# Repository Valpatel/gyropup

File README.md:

<div align="center">

<h1 id="gyropup"><picture style="display:block;max-width:640px;margin:0 auto"><source media="(prefers-reduced-motion: reduce)" srcset="docs/img/hero/gyropup-title-still.svg"></picture></h1>

<p>
<picture style="display:block;max-width:640px;margin:0 auto"><source media="(prefers-reduced-motion: reduce)" srcset="docs/img/navigation/project-map-still.svg"></picture>
<a href="https://cad-agent.valpatel.com/"><picture style="display:block;width:142px;max-width:100%;margin:10px auto"><source media="(prefers-reduced-motion: reduce)" srcset="docs/img/hero/made-with-cad-agent-still.svg"></picture></a>
A fictional playground. <a href="docs/program/physical-progress.md">Follow the real build evidence.</a><br>
<a href="https://gyropup.com/designer/sim.html">Play</a> · <a href="https://gyropup.com/designer/build.html">Build</a> · <a href="docs/README.md#design-and-qualification">Understand</a> · <a href=".github/CONTRIBUTING.md">Contribute</a>
</p>

</div>

## What is it?

A research robot designed to balance on two wheel-legs, with a foam-ball turret: CAD and simulation in the open.
Explore the [browser playground](https://gyropup.com/designer/sim.html), the
[design](docs/README.md#design-and-qualification) and [dated physical evidence](docs/program/physical-progress.md).

<p align="center">
<br>
Committed CAD baseline · <a href="docs/guide/project-overview.md#keeping-the-design-illustration-current">Source and context</a> · <a href="https://github.com/Valpatel/gyropup/issues/193">Battery placement work</a>.
</p>

## Why is it cool?

- Wheel-legs bring rolling, stepping and balance into one research problem.
- Open models make the design explorable in your browser.
- Gyropup evolves with cad-agent through good sources, evaluation, independent review and reusable methods.

Follow the [leg, turret and body build paths](docs/guide/project-overview.md#follow-the-build),
or browse the [published progress and reports](https://gyropup.com/designer/progress.html).

## How do I join in?

Start with [Contributing](.github/CONTRIBUTING.md), then choose a scoped issue from
[program #31](https://github.com/Valpatel/gyropup/issues/31). The [project guide](docs/guide/project-overview.md)
and [documentation map](docs/README.md) lead to the hardware, software, tools, tests and local website workflow.

**Unsafe research prototypes; not for sale.** Read the [prototype warning](docs/guide/prototype-safety.md).

[MIT](LICENSE) · [Licensing and vendor boundaries](docs/guide/project-overview.md#licence).

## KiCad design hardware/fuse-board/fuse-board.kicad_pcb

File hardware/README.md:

# Hardware: one folder per component

Physical design, component specifications and generated artifacts live here in separate homes:
[CAD](cad/README.md), [catalog](catalog/SCHEMA.md), [design inputs](designs/),
[generated exports](exports/) and [supplier acquisition records](vendor/).
Supplier payloads retain their original license and exclusion boundaries. Firmware and host control live in [software](../software/README.md).

Everything the repository knows about each bought or owned component, in one place per part: where its manual is,
how it connects, how it is configured, which code drives it, which units are in hand and how to bring it up. The
design itself stays where it is (the catalog, the docs, the CAD); these folders point at it and hold the parts that
belong to one component: its versioned config, its inventory and its bring-up page.

```mermaid
flowchart TB
  HW["hardware/"] --> A["actuators/"] & D["drives/"] & S["sensors/"] & P["power/"] & C["compute/"] & M["comms/"] & T["turret/"]
  A --> A1["rs04"] & A2["wheel-hub-motor"]
  D --> D1["flipsky-75100"]
  S --> S1["vn100-imu"] & S2["vlp16-lidar"] & S3["d435-depth-camera"]
  P --> P1["ina228-monitor"] & P2["dcb609-packs"]
  C --> C1["balance-mcu"] & C2["robot-computer"]
  M --> M1["pcan-usb"]
  T --> T1["turret-controller"]
  HW --> PCB["PCB projects (unchanged):<br/>fuse-board, carrier-packaging, carrier-pan-protection"]
```

## The map

| Folder | Component | In hand | State |
|---|---|---|---|
| [actuators/rs04/](actuators/rs04/README.md) | RobStride RS-04 leg motors | 4 (arrived 2026-11-03) | profiles, inventory, [bring-up](actuators/rs04/bring-up.md), the [motor tool](../docs/software/rs04-motor-tool.md) |
| [actuators/wheel-hub-motor/](actuators/wheel-hub-motor/README.md) | 10 in hoverboard-class hub motors (D69) | none | to buy and measure (W1) |
| [drives/flipsky-75100/](drives/flipsky-75100/README.md) | Flipsky 75100 VESCs for the wheels | none | VESC Tool settings recorded |
| [sensors/vn100-imu/](sensors/vn100-imu/README.md) | VectorNav VN-100 Rugged | 1 (the owner's) | boot registers recorded |
| [sensors/vlp16-lidar/](sensors/vlp16-lidar/README.md) | Velodyne VLP-16 | 1 (the owner's) | interfaces only |
| [sensors/d435-depth-camera/](sensors/d435-depth-camera/README.md) | RealSense D435 x 2 | 2 (the owner's) | interfaces only |
| [power/ina228-monitor/](power/ina228-monitor/README.md) | INA228 bus monitor and its shunt | none | shunt builds recorded |
| [power/dcb609-packs/](power/dcb609-packs/README.md) | DeWalt DCB609 packs and dock adapters | 2 (the owner's) | firmware limits recorded |
| [compute/balance-mcu/](compute/balance-mcu/README.md) | STM32G474 balance MCU board and CAN transceivers | none | pins and buses |
| [compute/robot-computer/](compute/robot-computer/README.md) | the robot's Jetson (J501 + AGX Orin in the design) | 1 (the owner's J501) | [hardware/deploy/jetson](../software/deploy/jetson/README.md); which Jetson is open |
| [comms/pcan-usb/](comms/pcan-usb/README.md) | PEAK PCAN-USB configuration adapter | 1 (the owner's) | used by the motor tool |
| [turret/turret-controller/](turret/turret-controller/README.md) | the turret's Feather M4 CAN electronics | none | a pointer to the turret docs |

**PCB projects** stay where they are, with their own layout: [fuse-board/](fuse-board/) (the generated KiCad fuse and
shunt board, D60; its doc is [docs/body-fuse-board.md](../docs/body/body-fuse-board.md)),
[carrier-packaging/](carrier-packaging/README.md) (issue #96) and
[carrier-pan-protection/](carrier-pan-protection/README.md) (issue #87). They are boards being designed, not components
bought; moving them under a category would break their build scripts' paths and their links for no gain, so they
are listed here and left alone.

## The skeleton every component folder keeps

`tools/check-hardware.py` checks it in CI (workflow `jetson-deploy`): every folder under a category has these, every
JSON file parses and names a `gyropup.*` schema, every relative link resolves, every sourced value in a
`gyropup.config/1` file still matches its source, and this map lists the folder. The RS-04 profiles
(`gyropup.rs04-profile/1`) are checked the same way by `python -m rig.rs04_profiles` and `rig/tests/test_rs04_vectors.py`.

| Part | What goes in it |
|---|---|
| `README.md` | a short intro, a diagram, then these sections in this order: **References**, **Interfaces**, **Config and profiles**, **Driver**, **Inventory**, **Bring-up and tests**, **Open questions** |
| References | where the manual, datasheet and CAD come from, **cited, never redistributed**: vendor files stay local, with a `SOURCE.txt` under `references/vendor/` saying where and when |
| `interfaces.md` | power, connectors, pinouts, buses and mounting, each row with its source |
| `config/` or `profiles/` | versioned JSON (`version`, `changes`) of the settings the component holds. A value taken from elsewhere has a `sources` entry (`c_define`, `json` + `pointer`, or `contains` + `text`) and the check fails when its source changes |
| Driver | a pointer to the code that talks to it (`rig/`, `firmware/`, `designer/kit/`): no code is copied here |
| `inventory.json` | `gyropup.inventory/1`: what was ordered and arrived (or is the owner's: `held`), and one record per unit. **Serials and ids are filled from the unit itself (a scan, an export, its label), never typed in or invented**; until then they are `null` |
| Bring-up and tests | the steps from a unit in its box to a working one, or a link to them; the software checks that cover it |

A section with nothing in it yet says **Not yet** and what would fill it. Nothing in these folders claims a test
that has not run.

## Adding a component

1. Pick its category; make `hardware/<category>/<name>/` (lower case, hyphens).
2. Copy the sections above into its README and fill what the repository already knows, with sources.
3. Add `interfaces.md` and `inventory.json` (empty `units` until one arrives), and `config/` when it holds settings.
4. Add a row to the map above and run `python3 tools/check-hardware.py`.
5. When it is bought, add the order to [docs/purchases.md](../docs/program/purchases.md) and the folder's inventory together.

## Deployment

What runs on the robot's computer (CAN bring-up, stable adapter names, the RS-04 bridge service) is in
[hardware/deploy/jetson](../software/deploy/jetson/README.md), installed by one idempotent command.

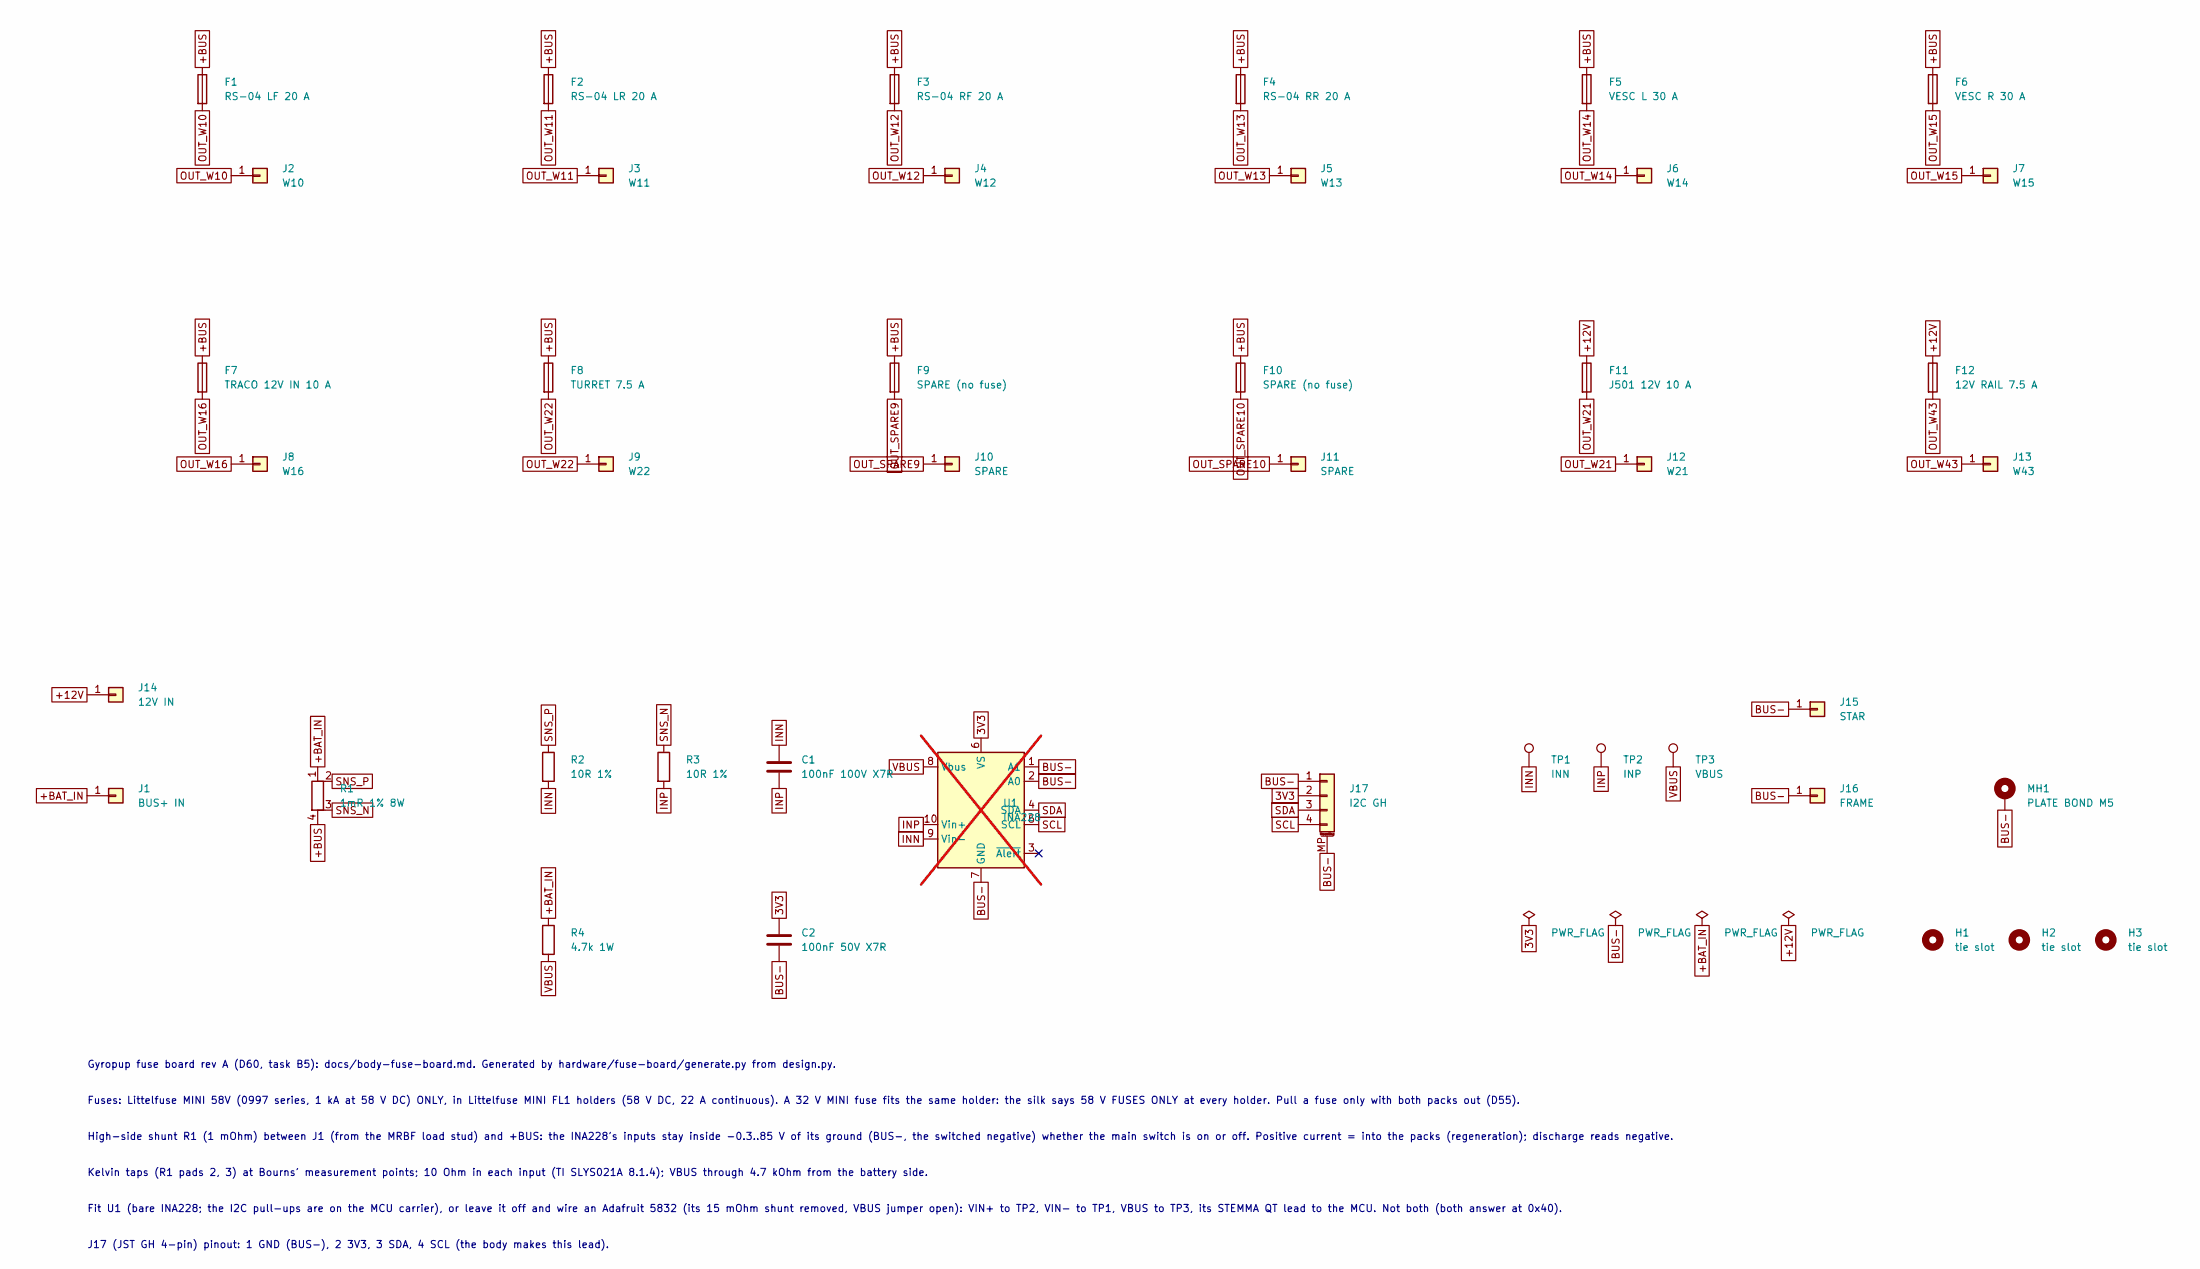
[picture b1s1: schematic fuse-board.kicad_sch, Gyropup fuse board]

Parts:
C1: 100nF 100V X7R; C_0603_1608Metric; LCSC C15725
C2: 100nF 50V X7R; C_0603_1608Metric; LCSC C14663
F1: RS-04 LF 20 A; Fuseholder_Blade_Mini_Littelfuse_FL1_178.6764.0001; MPN Littelfuse 178.6764.0001 (MINI FL1, 58 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; LCSC C142933
F2: RS-04 LR 20 A; Fuseholder_Blade_Mini_Littelfuse_FL1_178.6764.0001; MPN Littelfuse 178.6764.0001 (MINI FL1, 58 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; LCSC C142933
F3: RS-04 RF 20 A; Fuseholder_Blade_Mini_Littelfuse_FL1_178.6764.0001; MPN Littelfuse 178.6764.0001 (MINI FL1, 58 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; LCSC C142933
F4: RS-04 RR 20 A; Fuseholder_Blade_Mini_Littelfuse_FL1_178.6764.0001; MPN Littelfuse 178.6764.0001 (MINI FL1, 58 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; LCSC C142933
F5: VESC L 30 A; Fuseholder_Blade_Mini_Littelfuse_FL1_178.6764.0001; MPN Littelfuse 178.6764.0001 (MINI FL1, 58 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; LCSC C142933
F6: VESC R 30 A; Fuseholder_Blade_Mini_Littelfuse_FL1_178.6764.0001; MPN Littelfuse 178.6764.0001 (MINI FL1, 58 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; LCSC C142933
F7: TRACO 12V IN 10 A; Fuseholder_Blade_Mini_Littelfuse_FL1_178.6764.0001; MPN Littelfuse 178.6764.0001 (MINI FL1, 58 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; LCSC C142933
F8: TURRET 7.5 A; Fuseholder_Blade_Mini_Littelfuse_FL1_178.6764.0001; MPN Littelfuse 178.6764.0001 (MINI FL1, 58 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; LCSC C142933
F9, F10: SPARE (no fuse); Fuseholder_Blade_Mini_Littelfuse_FL1_178.6764.0001; MPN Littelfuse 178.6764.0001 (MINI FL1, 58 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; LCSC C142933
F11: J501 12V 10 A; Fuseholder_Blade_Mini_Littelfuse_FL1_178.6764.0001; MPN Littelfuse 178.6764.0001 (MINI FL1, 58 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; LCSC C142933
F12: 12V RAIL 7.5 A; Fuseholder_Blade_Mini_Littelfuse_FL1_178.6764.0001; MPN Littelfuse 178.6764.0001 (MINI FL1, 58 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; LCSC C142933
H1, H2, H3: tie slot; Slot_NPTH_4.0x10.0mm
J1: BUS+ IN; LugStud_M6_Pad12.0mm_Drill6.4mm_Via8; MPN M6 stud: socket head down through the l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
J2: W10; LugStud_M4_Pad7.0mm_Drill4.3mm_Via8; MPN M4 stud: socket head down through the l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
J3: W11; LugStud_M4_Pad7.0mm_Drill4.3mm_Via8; MPN M4 stud: socket head down through the l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
J4: W12; LugStud_M4_Pad7.0mm_Drill4.3mm_Via8; MPN M4 stud: socket head down through the l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
J5: W13; LugStud_M4_Pad7.0mm_Drill4.3mm_Via8; MPN M4 stud: socket head down through the l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
J6: W14; LugStud_M4_Pad7.0mm_Drill4.3mm_Via8; MPN M4 stud: socket head down through the l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
J7: W15; LugStud_M4_Pad7.0mm_Drill4.3mm_Via8; MPN M4 stud: socket head down through the l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
J8: W16; LugStud_M4_Pad7.0mm_Drill4.3mm_Via8; MPN M4 stud: socket head down through the l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
J9: W22; LugStud_M4_Pad7.0mm_Drill4.3mm_Via8; MPN M4 stud: socket head down through the l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
J10, J11: SPARE; LugStud_M4_Pad7.0mm_Drill4.3mm_Via8; MPN M4 stud: socket head down through the l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
J12: W21; LugStud_M4_Pad7.0mm_Drill4.3mm_Via8; MPN M4 stud: socket head down through the l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
J13: W43; LugStud_M4_Pad7.0mm_Drill4.3mm_Via8; MPN M4 stud: socket head down through the l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
J14: 12V IN; LugStud_M4_Pad7.0mm_Drill4.3mm_Via8; MPN M4 stud: socket head down through the l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
J15: STAR; LugStud_M4_Pad7.0mm_Drill4.3mm_Via8; MPN M4 stud: socket head down through the l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
J16: FRAME; LugStud_M4_Pad7.0mm_Drill4.3mm_Via8; MPN M4 stud: socket head down through the l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
J17: I2C GH; JST_GH_SM04B-GHS-TB_1x04-1MP_P1.25mm_Horizontal; MPN JST SM04B-GHS-TB; LCSC C189895
MH1: PLATE BOND M5; MountingHole_M5_Pad10.0mm_Drill5.3mm_Via8_Bond
R1: 1mR 1% 8W; R_Shunt_Bourns_CSS2H-3920_Kelvin; MPN Bourns CSS2H-3920R-1L00F; LCSC C4087295
R2, R3: 10R 1%; R_0603_1608Metric; LCSC C22859
R4: 4.7k 1W; R_2512_6332Metric; LCSC C163339
TP1: INN; TestPoint_THTPad_D2.0mm_Drill1.0mm
TP2: INP; TestPoint_THTPad_D2.0mm_Drill1.0mm
TP3: VBUS; TestPoint_THTPad_D2.0mm_Drill1.0mm
U1: INA228; TSSOP-10_3x3mm_P0.5mm; MPN TI INA228AIDGSR; LCSC C2887910; not fitted

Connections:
3V3: C2.1, J17.2, U1.6 (VS)
+12V: F11.1, F12.1, J14.1
+BAT_IN: J1.1, R1.1, R4.1
+BUS: F1.1, F2.1, F3.1, F4.1, F5.1, F6.1, F7.1, F8.1, F9.1, F10.1, R1.4
BUS-: C2.2, J15.1, J16.1, J17.1, J17.MP (MountPin), MH1.1, U1.1 (A1), U1.2 (A0), U1.7 (GND)
INN: C1.1, R2.2, TP1.1, U1.9 (Vin-)
INP: C1.2, R3.2, TP2.1, U1.10 (Vin+)
OUT_SPARE9: F9.2, J10.1
OUT_SPARE10: F10.2, J11.1
OUT_W10: F1.2, J2.1
OUT_W11: F2.2, J3.1
OUT_W12: F3.2, J4.1
OUT_W13: F4.2, J5.1
OUT_W14: F5.2, J6.1
OUT_W15: F6.2, J7.1
OUT_W16: F7.2, J8.1
OUT_W21: F11.2, J12.1
OUT_W22: F8.2, J9.1
OUT_W43: F12.2, J13.1
SCL: J17.4, U1.5 (SCL)
SDA: J17.3, U1.4 (SDA)
SNS_N: R1.3, R3.1
SNS_P: R1.2, R2.1
VBUS: R4.2, TP3.1, U1.8 (Vbus)

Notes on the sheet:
Gyropup fuse board rev A (D60, task B5): docs/body-fuse-board.md. Generated by hardware/fuse-board/generate.py from design.py.
Fuses: Littelfuse MINI 58V (0997 series, 1 kA at 58 V DC) ONLY, in Littelfuse MINI FL1 holders (58 V DC, 22 A continuous). A 32 V MINI fuse fits the same holder: the silk says 58 V FUSES ONLY at every holder. Pull a fuse only with both packs out (D55).
High-side shunt R1 (1 mOhm) between J1 (from the MRBF load stud) and +BUS: the INA228's inputs stay inside -0.3..85 V of its ground (BUS-, the switched negative) whether the main switch is on or off. Positive current = into the packs (regeneration); discharge reads negative.
Kelvin taps (R1 pads 2, 3) at Bourns' measurement points; 10 Ohm in each input (TI SLYS021A 8.1.4); VBUS through 4.7 kOhm from the battery side.
Fit U1 (bare INA228; the I2C pull-ups are on the MCU carrier), or leave it off and wire an Adafruit 5832 (its 15 mOhm shunt removed, VBUS jumper open): VIN+ to TP2, VIN- to TP1, VBUS to TP3, its STEMMA QT lead to the MCU. Not both (both answer at 0x40).
J17 (JST GH 4-pin) pinout: 1 GND (BUS-), 2 3V3, 3 SDA, 4 SCL (the body makes this lead).

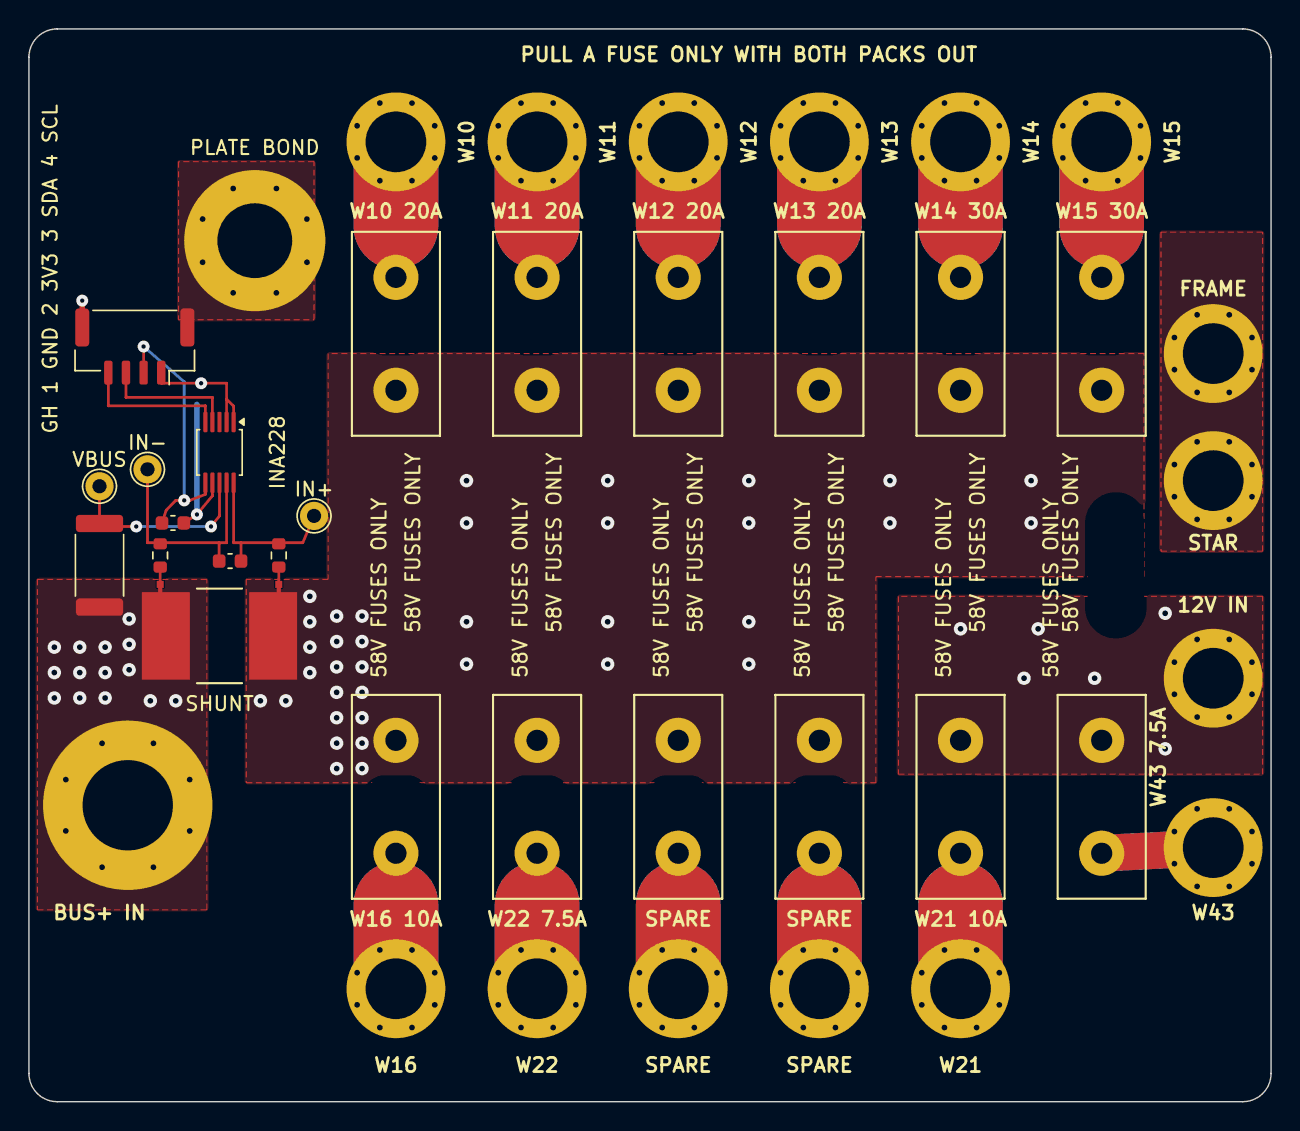
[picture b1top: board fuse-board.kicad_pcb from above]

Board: 2 copper layers, 88.0 x 76.0 mm, 43 parts (0 on the bottom side), 24 nets.

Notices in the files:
README.md:
Licence: MIT
